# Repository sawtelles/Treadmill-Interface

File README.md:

# Treadmill-Interface
 Treadmill Interface 
Provides an interface to a treadmill that uses an incremental encoder to monitor speed and distance.
The speed and distance are calculated at each increment of the encoder. Time, speed, and distance are sent out a serial-USB port. The minimum time between readinsg can be set, as well as the time to wait to set zero speed.
The absolute value of speed is also sent out to an SMA connector as an analog signal. Direction is sent out another SMA connector as a 3.3V digital signal. 
The design utilizes a Teensy 4.0.
The encoder voltage provided is 5 volts.

PCB design done in Eagle
Firmware design in Arduino with Teensy extensions
Processor - Teensy 4.0

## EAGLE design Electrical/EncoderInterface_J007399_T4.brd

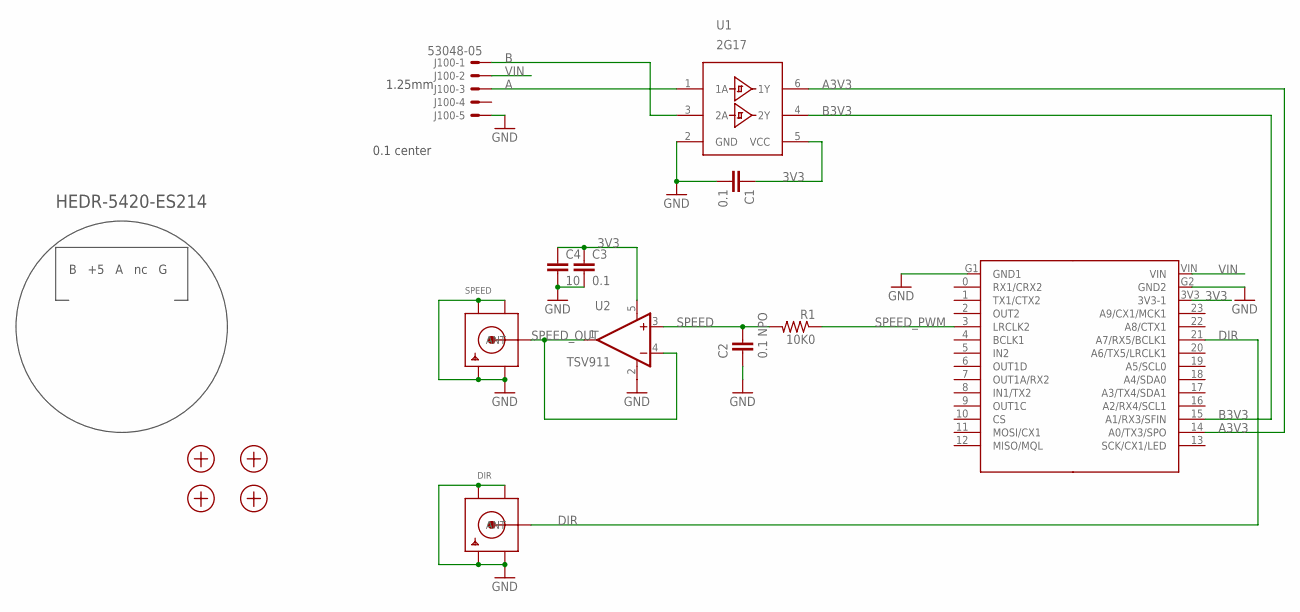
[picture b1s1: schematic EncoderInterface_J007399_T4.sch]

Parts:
C1, C3: 0.1; 0603S
C2: 0.1 NPO; 1206S
C4: 10; 1206S
DIR: SMACONNECTOR; SMA90_DIP
J100: 53048-05
M1A: TEENSY40A; TEENSY40-A
M1B: TEENSY40B; TEENSY40-B
R1: 10K0; 0805S
S1, S2, S3, S4: SCREW2-56SCREW; 2-56SOCKET
SPEED: SMACONNECTOR; SMA90_DIP
U1: 2G17; SOT23-6
U2: TSV911; SOT23-5

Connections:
3V3: C1.1, C3.1, C4.1, M1B.3V3 (3V3-1), U1.5 (VCC), U2.5 (V+)
A: J100.3, U1.1 (1A)
A3V3: M1B.14 (A0/TX3/SPO), U1.6 (1Y)
B: J100.1, U1.3 (2A)
B3V3: M1B.15 (A1/RX3/SFIN), U1.4 (2Y)
DIR: DIR.ANTENNA (ANT), M1B.21 (A7/RX5/BCLK1)
GND: C1.2, C2.2, C3.2, C4.2, DIR.GND1, DIR.GND2, DIR.GND3, DIR.GND4, J100.5, M1A.G1 (GND1), M1B.G2 (GND2), SPEED.GND1, SPEED.GND2, SPEED.GND3, SPEED.GND4, U1.2 (GND), U2.2 (V-)
SPEED: C2.1, R1.2, U2.3 (+IN)
SPEED_OUT: SPEED.ANTENNA (ANT), U2.1 (OUT), U2.4 (-IN)
SPEED_PWM: M1A.3 (LRCLK2), R1.1
VIN: J100.2, M1B.VIN

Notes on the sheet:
B +5 A nc G
HEDR-5420-ES214
0.1 center
1.25mm

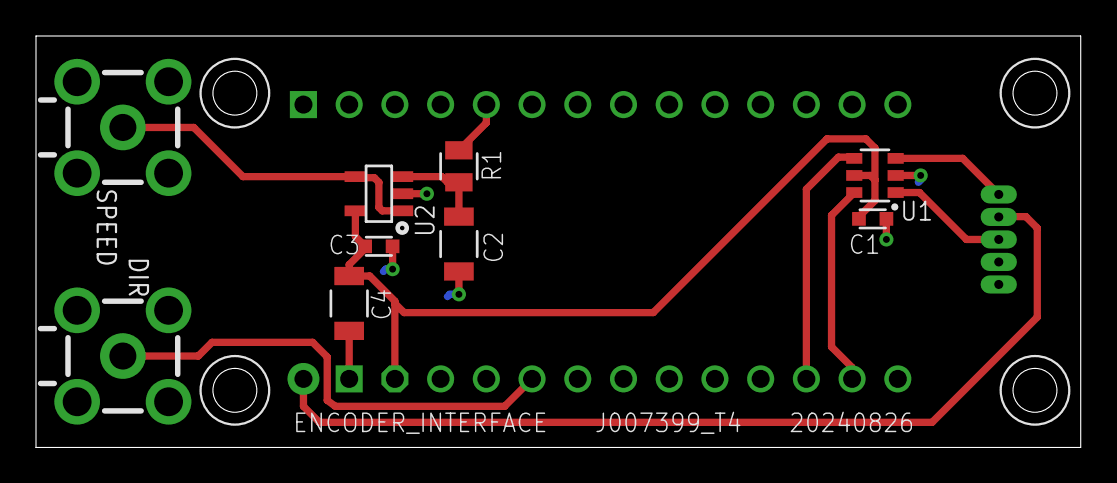
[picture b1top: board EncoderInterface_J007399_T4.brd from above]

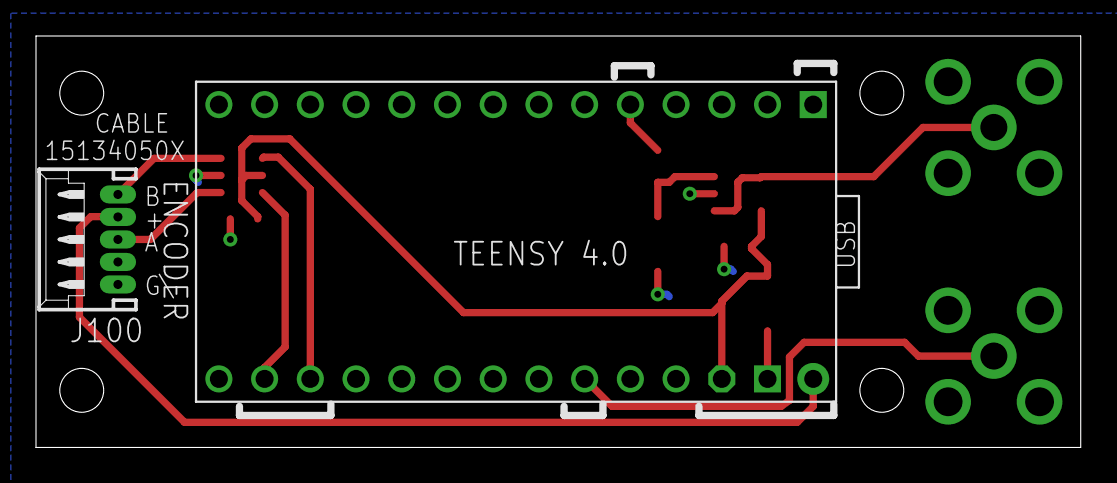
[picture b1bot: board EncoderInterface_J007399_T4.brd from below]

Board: 2 copper layers, 58.0 x 22.9 mm, 16 parts (3 on the bottom side), 11 nets.

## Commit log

2024-09-09 Treadmill interface based on Teensy 4.0 - initial design
    Treadmill encoder interface updated from earlier Teensy 3.2 design, to utilize currently available Teensy 4.0.
2026-03-31 add zero_offset code

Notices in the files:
parts and their libraries:
SparkFun: Licensing: CC v3.0 Share-Alike You are welcome to use this library for commercial purposes.
